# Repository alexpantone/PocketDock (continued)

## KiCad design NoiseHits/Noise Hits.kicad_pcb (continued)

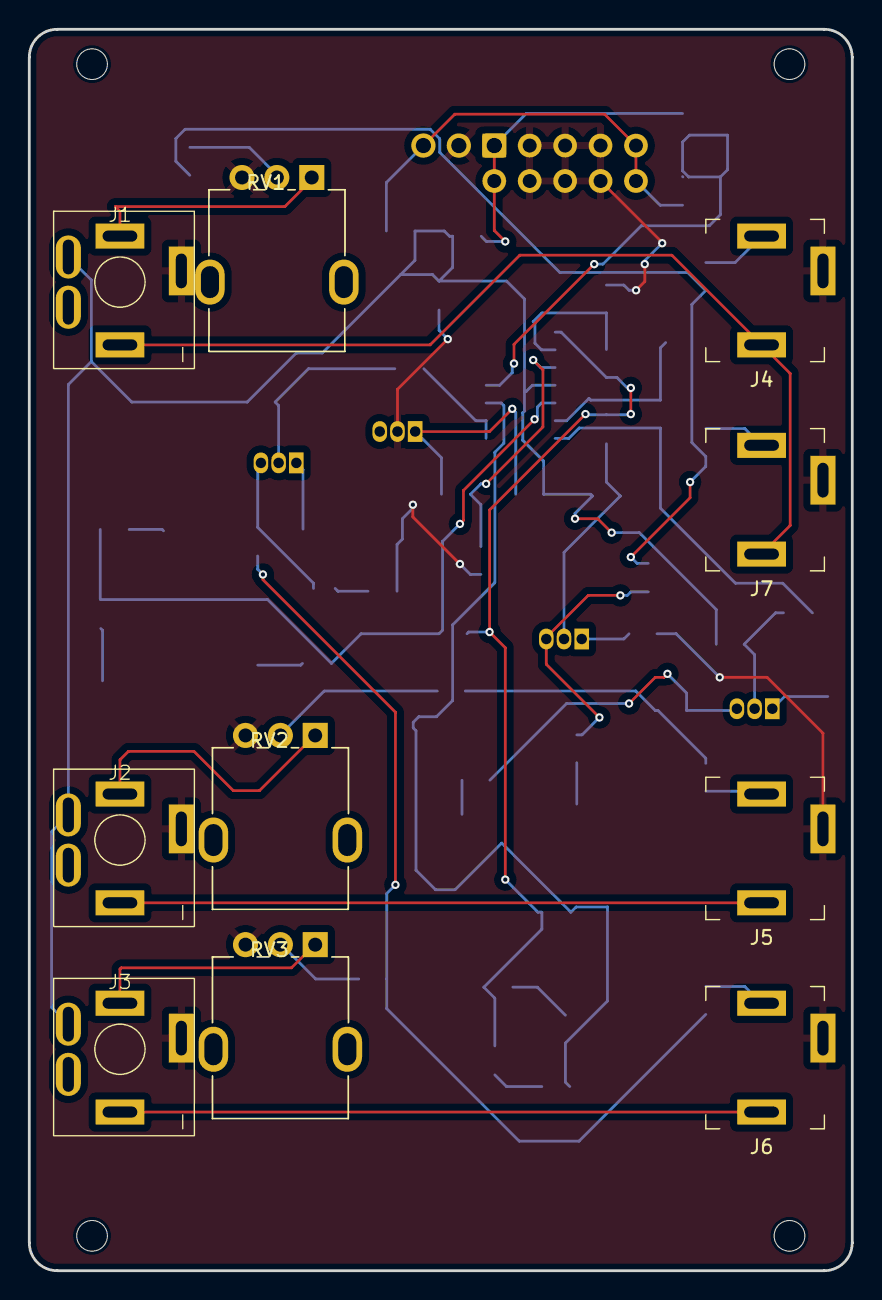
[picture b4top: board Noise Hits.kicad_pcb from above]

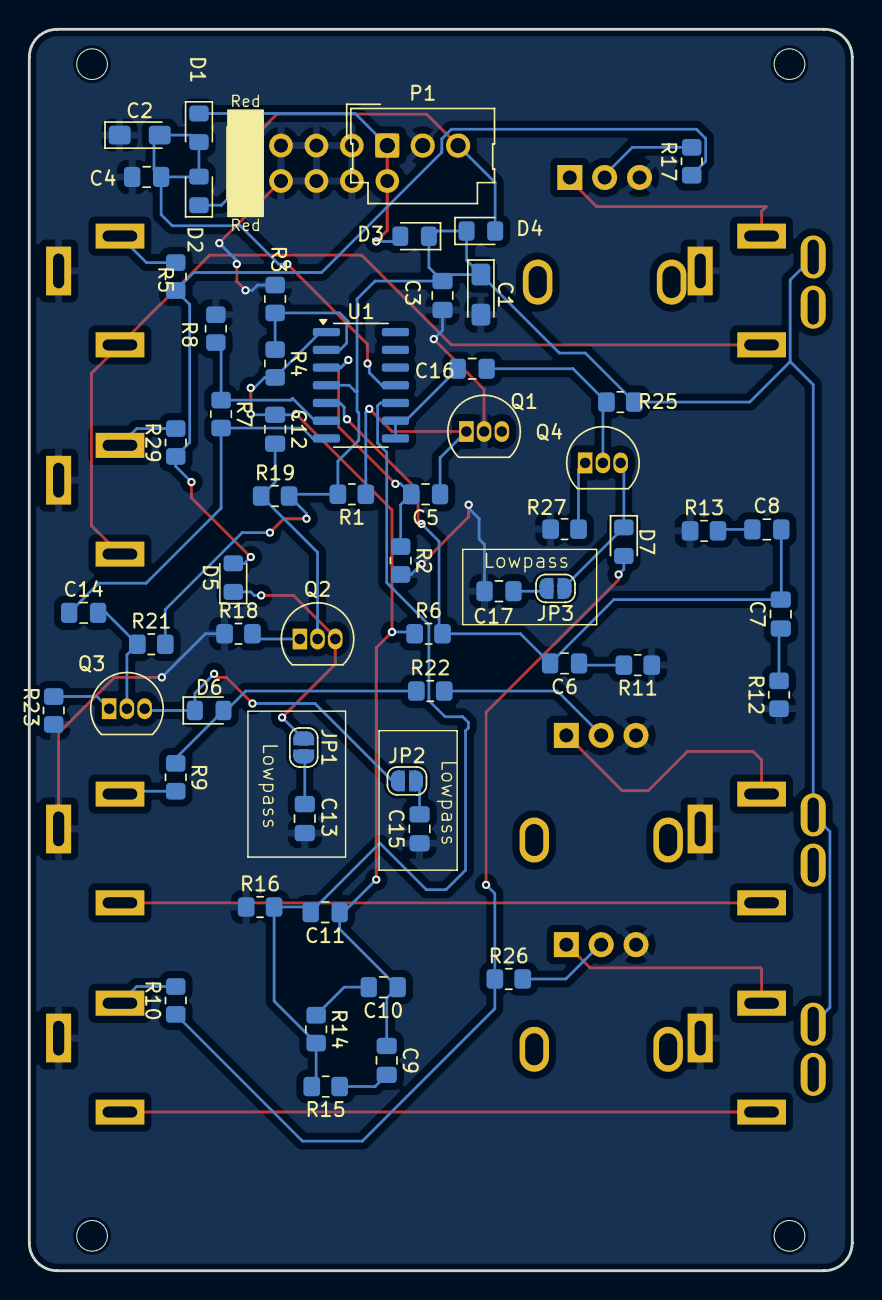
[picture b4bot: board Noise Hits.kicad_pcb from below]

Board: 2 copper layers, 59.0 x 89.0 mm, 74 parts (60 on the bottom side), 47 nets.

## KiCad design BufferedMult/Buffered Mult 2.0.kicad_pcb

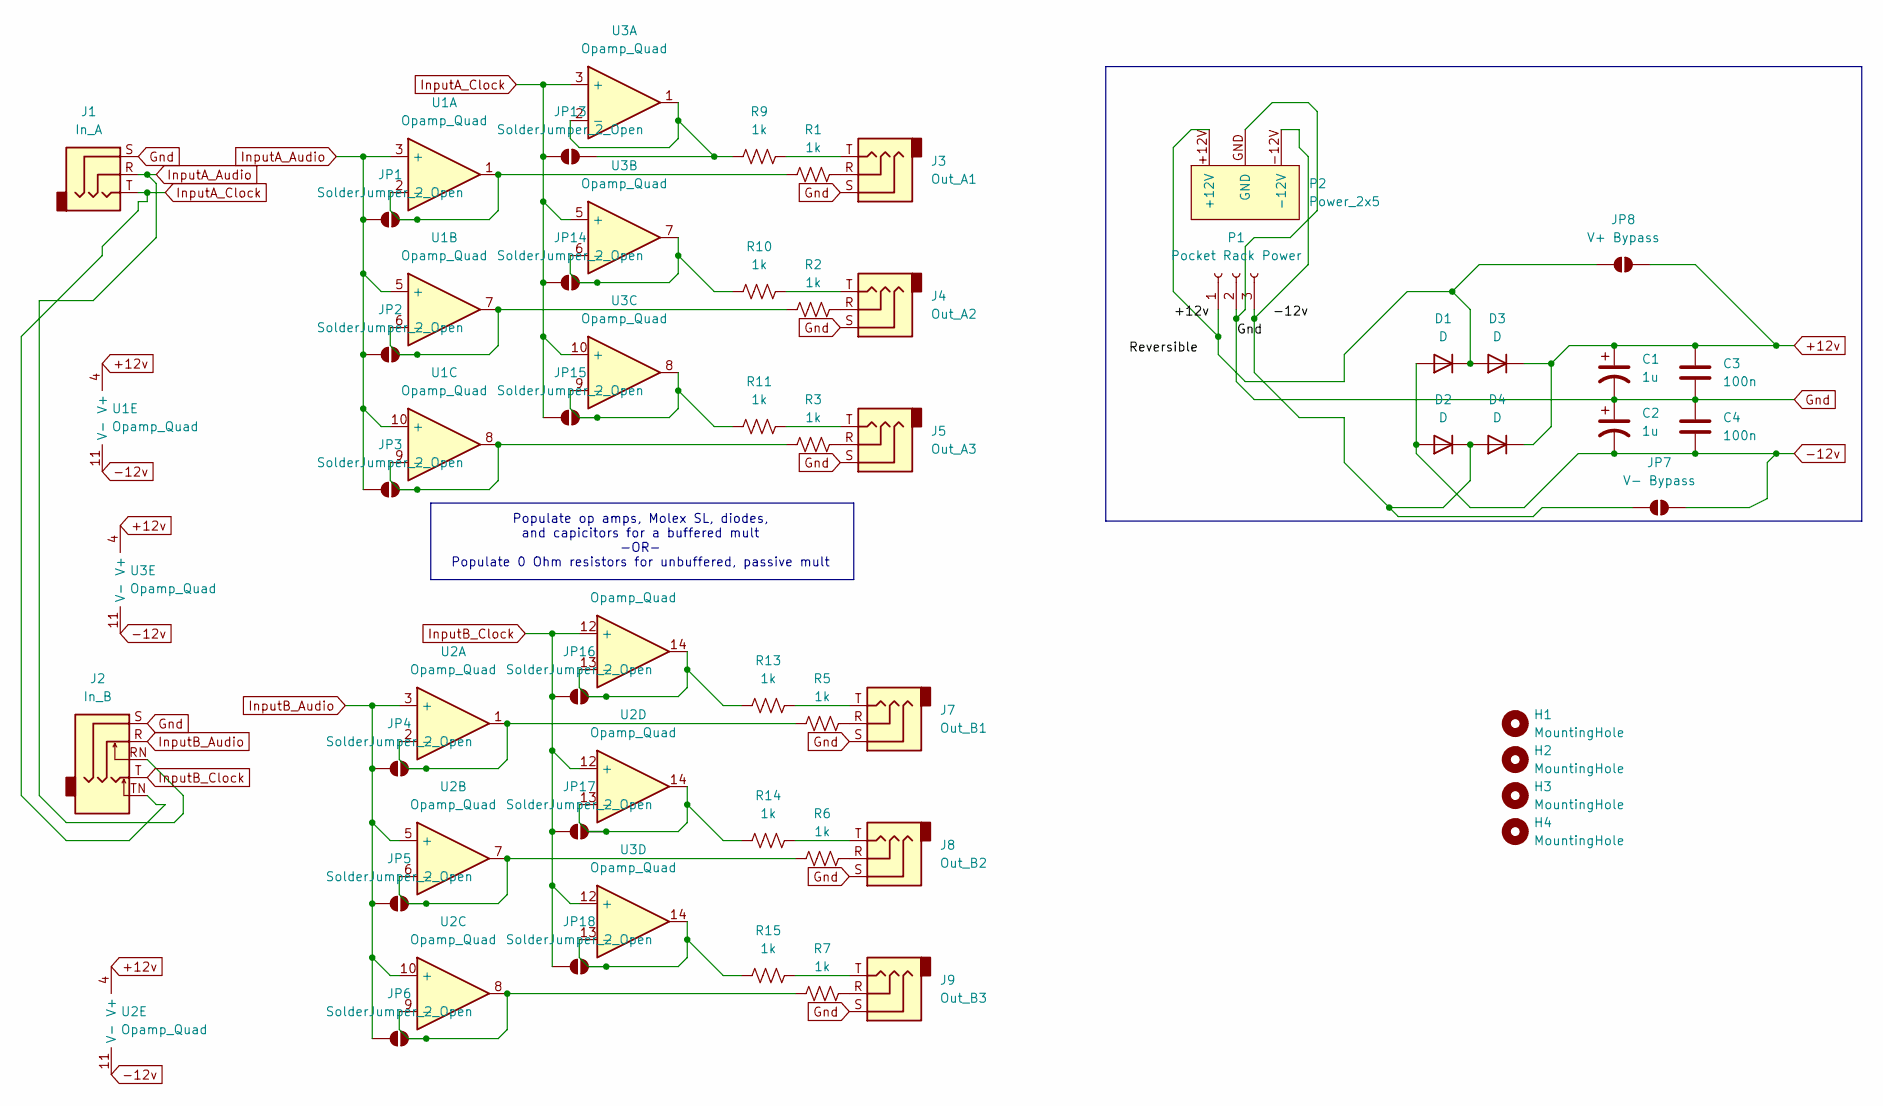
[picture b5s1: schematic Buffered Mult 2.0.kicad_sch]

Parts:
C1, C2: 1u; CP_EIA-3216-10_Kemet-I_Pad1.58x1.35mm_HandSolder
C3, C4: 100n; C_0805_2012Metric_Pad1.18x1.45mm_HandSolder
D1, D2, D3, D4: D; D_0805_2012Metric_Pad1.15x1.40mm_HandSolder
H1, H2, H3, H4: MountingHole; MountingHole_2.2mm_M2
J1: In_A; Jack_3.5mm_QingPu_WQP-PJ301CM
J2: In_B; Jack_3.5mm_QingPu_WQP-PJ358
J3: Out_A1; Jack_3.5mm_QingPu_WQP-PJ301CM
J4: Out_A2; Jack_3.5mm_QingPu_WQP-PJ301CM
J5: Out_A3; Jack_3.5mm_QingPu_WQP-PJ301CM
J7: Out_B1; Jack_3.5mm_QingPu_WQP-PJ301CM
J8: Out_B2; Jack_3.5mm_QingPu_WQP-PJ301CM
J9: Out_B3; Jack_3.5mm_QingPu_WQP-PJ301CM
JP1, JP2, JP3, JP4, JP5, JP6, JP13, JP14, JP15, JP16, JP17, JP18: SolderJumper_2_Open; SolderJumper-2_P1.3mm_Open_Pad1.0x1.5mm
JP7: V- Bypass; SolderJumper-2_P1.3mm_Open_TrianglePad1.0x1.5mm
JP8: V+ Bypass; SolderJumper-2_P1.3mm_Open_TrianglePad1.0x1.5mm
P1: Pocket Rack Power; Molex_SL_171971-0003_1x03_P2.54mm_Vertical
P2: Power_2x5; Power_2x5_Vertical
R1, R2, R3, R5, R6, R7, R9, R10, R11, R13, R14, R15: 1k; R_0805_2012Metric_Pad1.20x1.40mm_HandSolder
U1, U2, U3: Opamp_Quad; SOIC-14_3.9x8.7mm_P1.27mm

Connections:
+12v: C1.1, C3.1, D3.1 (K), D4.1 (K), JP8.2 (B), U1.4 (V+), U2.4 (V+), U3.4 (V+)
-12v: C2.2, C4.2, D1.2 (A), D2.2 (A), JP7.2 (B), U1.11 (V-), U2.11 (V-), U3.11 (V-)
Gnd: C1.2, C2.1, C3.2, C4.1, J1.S, J2.S, J3.S, J4.S, J5.S, J7.S, J8.S, J9.S, P1.2, P2.GND
InputA_Audio: J1.R, J2.RN, JP1.1 (A), JP2.1 (A), JP3.1 (A), U1.3 (+), U1.5 (+), U1.10 (+)
InputA_Clock: J1.T, J2.TN, JP13.1 (A), JP14.1 (A), JP15.1 (A), U3.3 (+), U3.5 (+), U3.10 (+)
InputB_Audio: J2.R, JP4.1 (A), JP5.1 (A), JP6.1 (A), U2.3 (+), U2.5 (+), U2.10 (+)
InputB_Clock: J2.T, JP16.1 (A), JP17.1 (A), JP18.1 (A), U1.12 (+), U2.12 (+), U3.12 (+)
unnamed: D1.1 (K), D3.2 (A), JP8.1 (A), P1.1, P2.+12V
unnamed: D2.1 (K), D4.2 (A), JP7.1 (A), P1.3, P2.-12V
unnamed: J3.R, R1.2
unnamed: J3.T, R9.2
unnamed: J4.R, R2.2
unnamed: J4.T, R10.2
unnamed: J5.R, R3.2
unnamed: J5.T, R11.2
unnamed: J7.R, R5.2
unnamed: J7.T, R13.2
unnamed: J8.R, R6.2
unnamed: J8.T, R14.2
unnamed: J9.R, R7.2
unnamed: J9.T, R15.2
unnamed: JP1.2 (B), R1.1, U1.1, U1.2 (-)
unnamed: JP2.2 (B), R2.1, U1.6 (-), U1.7
unnamed: JP3.2 (B), R3.1, U1.8, U1.9 (-)
unnamed: JP4.2 (B), R5.1, U2.1, U2.2 (-)
unnamed: JP5.2 (B), R6.1, U2.6 (-), U2.7
unnamed: JP6.2 (B), R7.1, U2.8, U2.9 (-)
unnamed: JP13.2 (B), R9.1, U3.1, U3.2 (-)
unnamed: JP14.2 (B), R10.1, U3.6 (-), U3.7
unnamed: JP15.2 (B), R11.1, U3.8, U3.9 (-)
unnamed: JP16.2 (B), R13.1, U1.13 (-), U1.14
unnamed: JP17.2 (B), R14.1, U2.13 (-), U2.14
unnamed: JP18.2 (B), R15.1, U3.13 (-), U3.14

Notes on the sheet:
Populate op amps, Molex SL, diodes, and capicitors for a buffered mult -OR- Populate 0 Ohm resistors for unbuffered, passive mult

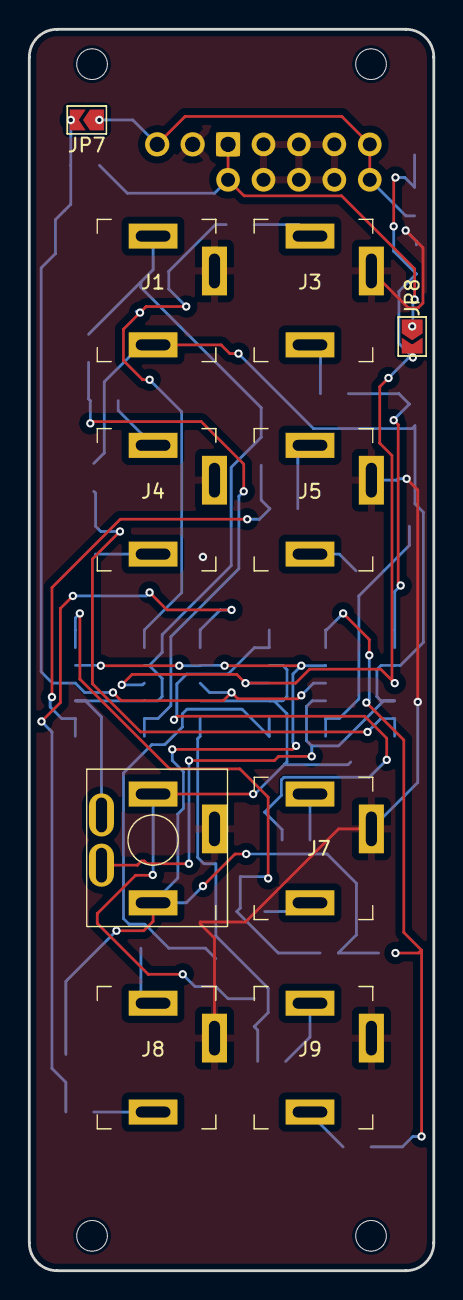
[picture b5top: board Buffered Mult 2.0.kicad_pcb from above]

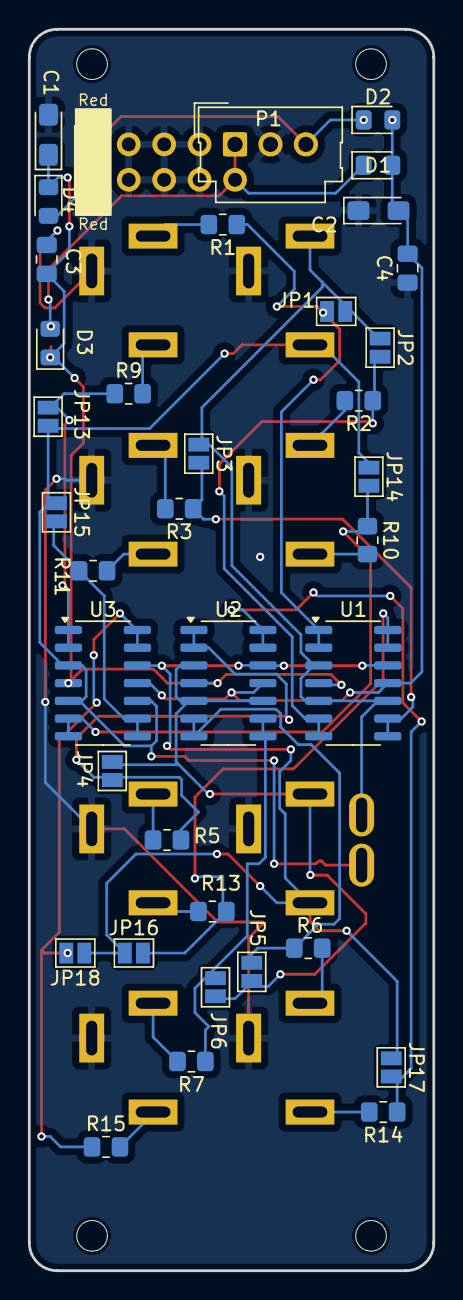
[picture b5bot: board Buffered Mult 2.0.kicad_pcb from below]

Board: 2 copper layers, 29.0 x 89.0 mm, 51 parts (37 on the bottom side), 33 nets.

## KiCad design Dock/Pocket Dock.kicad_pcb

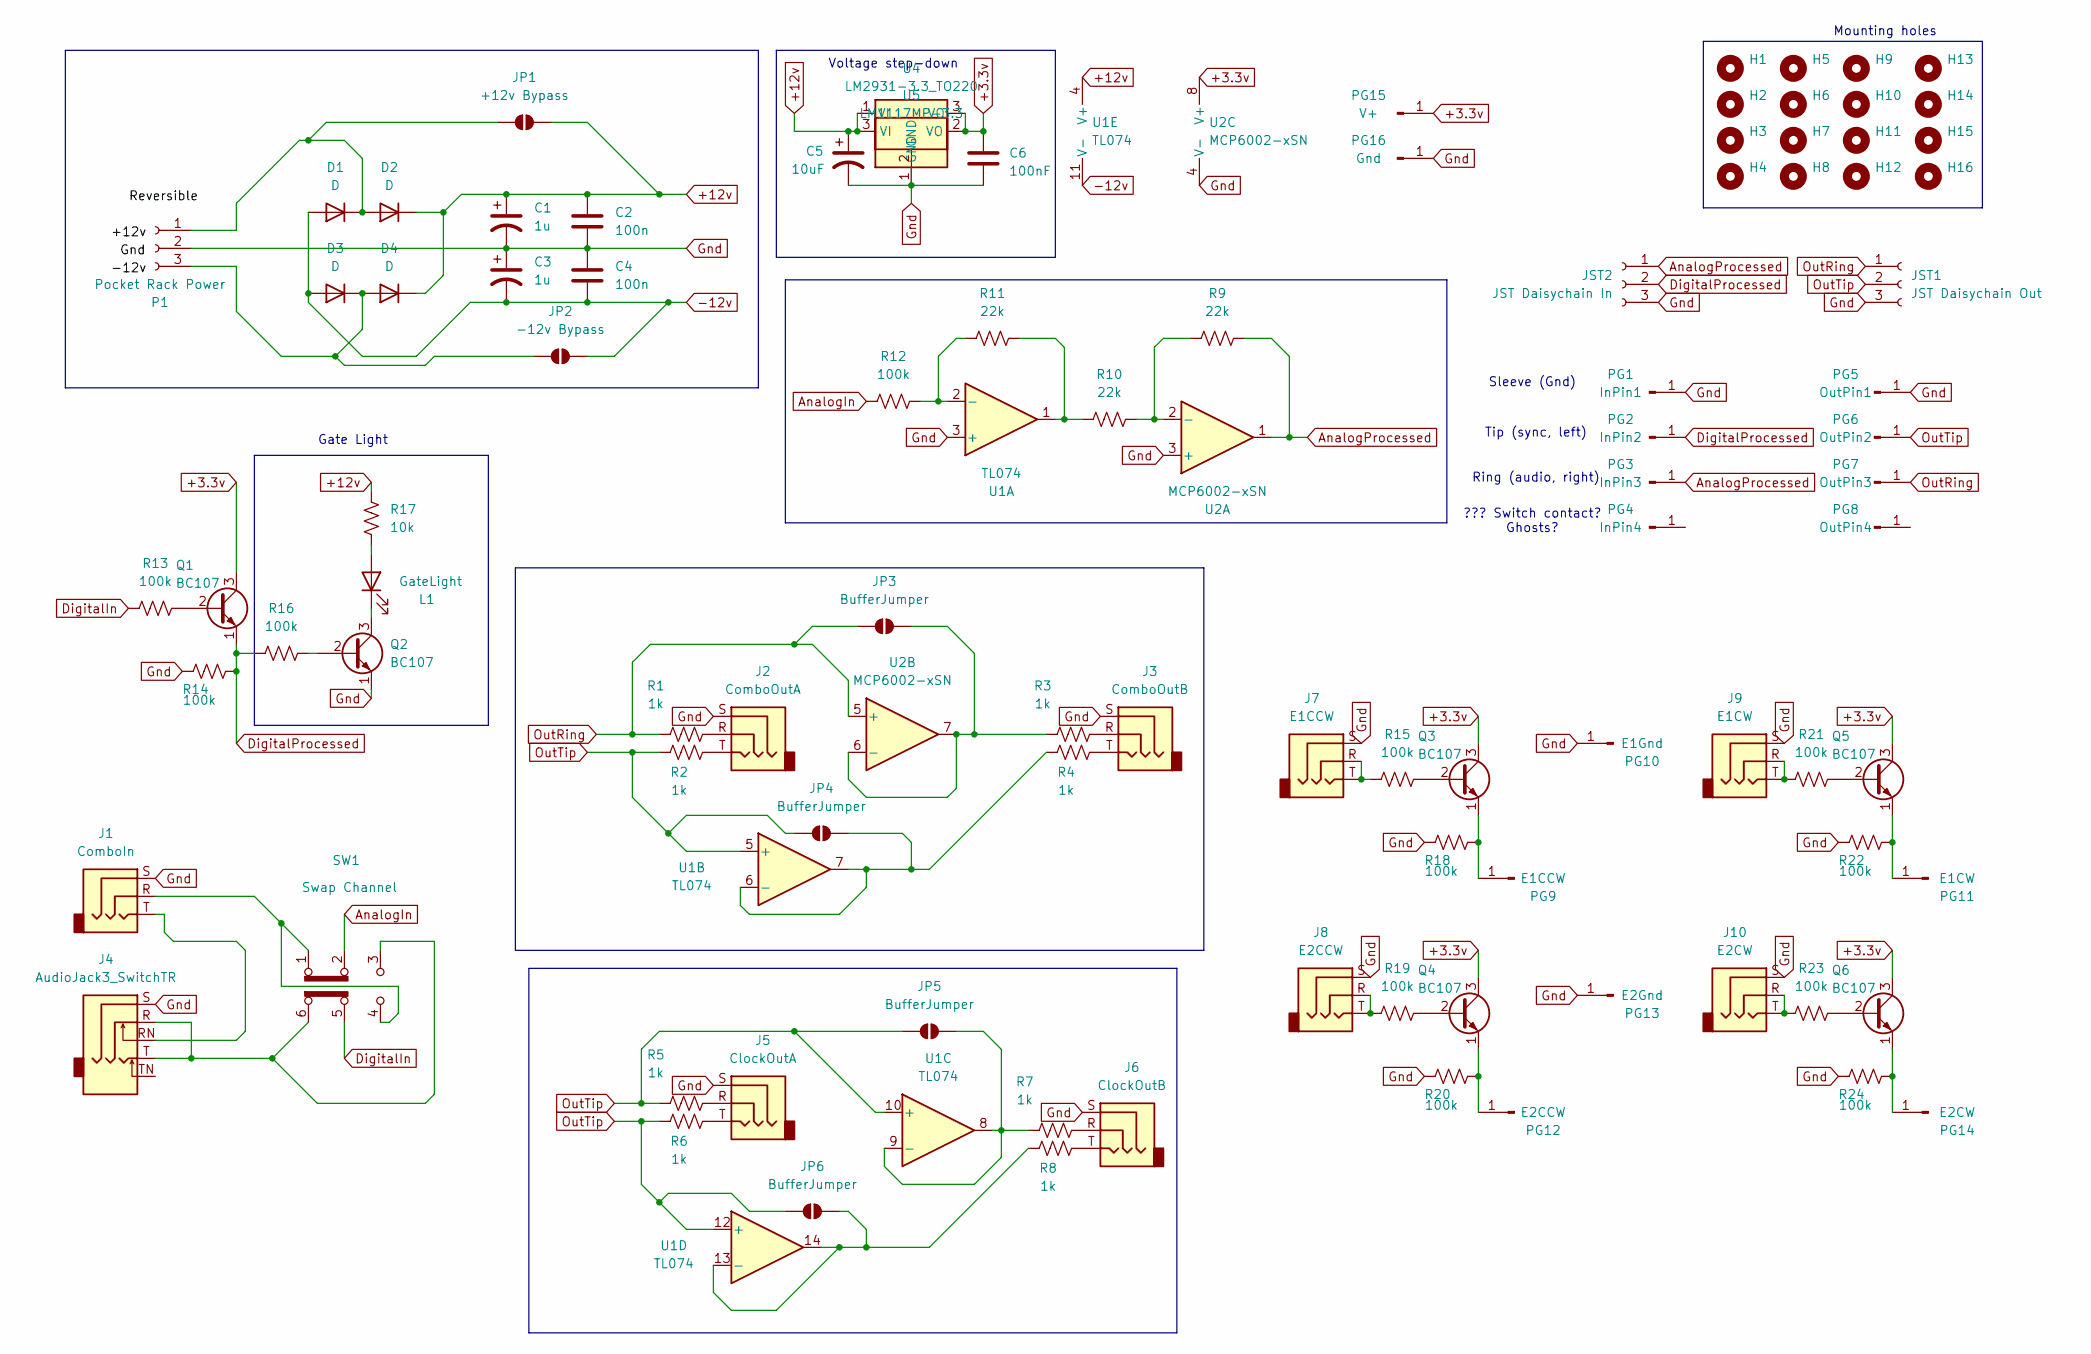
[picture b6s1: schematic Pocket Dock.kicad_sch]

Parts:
C1, C3: 1u; CP_EIA-3216-10_Kemet-I_Pad1.58x1.35mm_HandSolder
C2, C4: 100n; C_0805_2012Metric_Pad1.18x1.45mm_HandSolder
C5: 10uF; C_0805_2012Metric_Pad1.18x1.45mm_HandSolder
C6: 100nF; C_0805_2012Metric_Pad1.18x1.45mm_HandSolder
D1, D2, D3, D4: D; D_0805_2012Metric_Pad1.15x1.40mm_HandSolder
H1, H2, H3, H4, H5, H6, H7, H8, H9, H10, H11, H12, H13, H14, H15, H16: MountingHole; MountingHole_2.2mm_M2
J1: ComboIn; Jack_3.5mm_QingPu_WQP-PJ301CM
J2: ComboOutA; Jack_3.5mm_QingPu_WQP-PJ301CM
J3: ComboOutB; Jack_3.5mm_QingPu_WQP-PJ301CM
J4: AudioJack3_SwitchTR; Jack_3.5mm_QingPu_WQP-PJ358
J5: ClockOutA; Jack_3.5mm_QingPu_WQP-PJ301CM
J6: ClockOutB; Jack_3.5mm_QingPu_WQP-PJ301CM
J7: E1CCW; Jack_3.5mm_QingPu_WQP-PJ301CM
J8: E2CCW; Jack_3.5mm_QingPu_WQP-PJ301CM
J9: E1CW; Jack_3.5mm_QingPu_WQP-PJ301CM
J10: E2CW; Jack_3.5mm_QingPu_WQP-PJ301CM
JP1: +12v Bypass; SolderJumper-2_P1.3mm_Open_TrianglePad1.0x1.5mm
JP2: -12v Bypass; SolderJumper-2_P1.3mm_Open_TrianglePad1.0x1.5mm
JP3, JP4, JP5, JP6: BufferJumper; SolderJumper-2_P1.3mm_Open_RoundedPad1.0x1.5mm
JST1: JST Daisychain Out; JST_XH_B3B-XH-A_1x03_P2.50mm_Vertical
JST2: JST Daisychain In; JST_XH_B3B-XH-A_1x03_P2.50mm_Vertical
L1: GateLight; LED_D3.0mm
P1: Pocket Rack Power; Molex_SL_171971-0003_1x03_P2.54mm_Vertical
PG1: InPin1; PinHeader_1x01_P2.00mm_Vertical
PG2: InPin2; PinHeader_1x01_P2.00mm_Vertical
PG3: InPin3; PinHeader_1x01_P2.00mm_Vertical
PG4: InPin4; PinHeader_1x01_P2.00mm_Vertical
PG5: OutPin1; PinHeader_1x01_P2.00mm_Vertical
PG6: OutPin2; PinHeader_1x01_P2.00mm_Vertical
PG7: OutPin3; PinHeader_1x01_P2.00mm_Vertical
PG8: OutPin4; PinHeader_1x01_P2.00mm_Vertical
PG9: E1CCW; PinHeader_1x01_P2.00mm_Vertical
PG10: E1Gnd; PinHeader_1x01_P2.00mm_Vertical
PG11: E1CW; PinHeader_1x01_P2.00mm_Vertical
PG12: E2CCW; PinHeader_1x01_P2.00mm_Vertical
PG13: E2Gnd; PinHeader_1x01_P2.00mm_Vertical
PG14: E2CW; PinHeader_1x01_P2.00mm_Vertical
PG15: V+; PinHeader_1x01_P2.00mm_Vertical
PG16: Gnd; PinHeader_1x01_P2.00mm_Vertical
Q1, Q2, Q3, Q4, Q5, Q6: BC107; SC-59_Handsoldering
R1, R2, R3, R4, R5, R6, R7, R8: 1k; R_0805_2012Metric_Pad1.20x1.40mm_HandSolder
R9, R10, R11: 22k; R_0805_2012Metric_Pad1.20x1.40mm_HandSolder
R12, R13, R14, R15, R16, R18, R19, R20, R21, R22, R23, R24: 100k; R_0805_2012Metric_Pad1.20x1.40mm_HandSolder
R17: 10k; R_0805_2012Metric_Pad1.20x1.40mm_HandSolder
SW1: Swap Channel; SW_E-Switch_EG1271_SPDT
U1: TL074; SOIC-14_3.9x8.7mm_P1.27mm
U2: MCP6002-xSN; SOIC-8_3.9x4.9mm_P1.27mm
U4: LM2931-3.3_TO220; TO-220-3_Vertical
U5: LM1117MP-3.3; SOT-223-3_TabPin2

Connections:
+3.3v: C6.1, PG15.1, Q1.3 (C), Q3.3 (C), Q4.3 (C), Q5.3 (C), Q6.3 (C), U2.8 (V+), U4.3 (VO), U5.2 (VO)
+12v: C1.1, C2.1, C5.1, D2.1 (K), D4.1 (K), JP1.2 (B), R17.1, U1.4 (V+), U4.1 (VI), U5.3 (VI)
-12v: C3.2, C4.2, D1.2 (A), D3.2 (A), JP2.2 (B), U1.11 (V-)
AnalogIn: R12.1, SW1.2 (B)
AnalogProcessed: JST2.1, PG3.1, R9.2, U2.1
DigitalIn: R13.2, SW1.5 (B)
DigitalProcessed: JST2.2, PG2.1, Q1.1 (E), R14.2, R16.1
Gnd: C1.2, C2.2, C3.1, C4.1, C5.2, C6.2, J1.S, J2.S, J3.S, J4.S, J5.S, J6.S, J7.S, J8.S, J9.S, J10.S, JST1.3, JST2.3, P1.2, PG1.1, PG5.1, PG10.1, PG13.1, PG16.1, Q2.1 (E), R14.1, R18.1, R20.1, R22.1, R24.1, U1.3 (+), U2.3 (+), U2.4 (V-), U4.2 (GND), U5.1 (GND)
unnamed: D1.1 (K), D2.2 (A), JP1.1 (A), P1.1
unnamed: D3.1 (K), D4.2 (A), JP2.1 (A), P1.3
unnamed: J1.R, SW1.1 (A), SW1.4 (A)
unnamed: J1.T, J4.RN
unnamed: J2.R, R1.2
unnamed: J2.T, R2.2
unnamed: J3.R, R3.2
unnamed: J3.T, R4.2
unnamed: J4.R, J4.T, SW1.3 (C), SW1.6 (C)
unnamed: J5.R, R5.2
unnamed: J5.T, R6.2
unnamed: J6.R, R7.2
unnamed: J6.T, R8.2
unnamed: J7.R, J7.T, R15.2
unnamed: J8.R, J8.T, R19.2
unnamed: J9.R, J9.T, R21.2
unnamed: J10.R, J10.T, R23.2
unnamed: JP3.2 (B), R3.1, U2.6 (-), U2.7
unnamed: JP4.2 (B), R4.1, U1.6 (-), U1.7
unnamed: JP5.2 (B), R7.1, U1.8, U1.9 (-)
unnamed: JP6.2 (B), R8.1, U1.13 (-), U1.14
unnamed: L1.2 (A), R17.2
unnamed: L1.1 (K), Q2.3 (C)
unnamed: PG9.1, Q3.1 (E), R18.2
unnamed: PG11.1, Q5.1 (E), R22.2
unnamed: PG12.1, Q4.1 (E), R20.2
unnamed: PG14.1, Q6.1 (E), R24.2
unnamed: Q1.2 (B), R13.1
unnamed: Q2.2 (B), R16.2
unnamed: Q3.2 (B), R15.1
unnamed: Q4.2 (B), R19.1
unnamed: Q5.2 (B), R21.1
unnamed: Q6.2 (B), R23.1
unnamed: R10.1, R11.2, U1.1
unnamed: R11.1, R12.2, U1.2 (-)
unnamed: R9.1, R10.2, U2.2 (-)
OutRing: JP3.1 (A), JST1.1, PG7.1, R1.1, U2.5 (+)
OutTip: JP4.1 (A), JP5.1 (A), JP6.1 (A), JST1.2, PG6.1, R2.1, R5.1, R6.1, U1.5 (+), U1.10 (+), U1.12 (+)

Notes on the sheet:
Mounting holes
??? Switch contact? Ghosts?
Ring (audio, right)
Gate Light
Voltage step-down
Sleeve (Gnd)
Tip (sync, left)

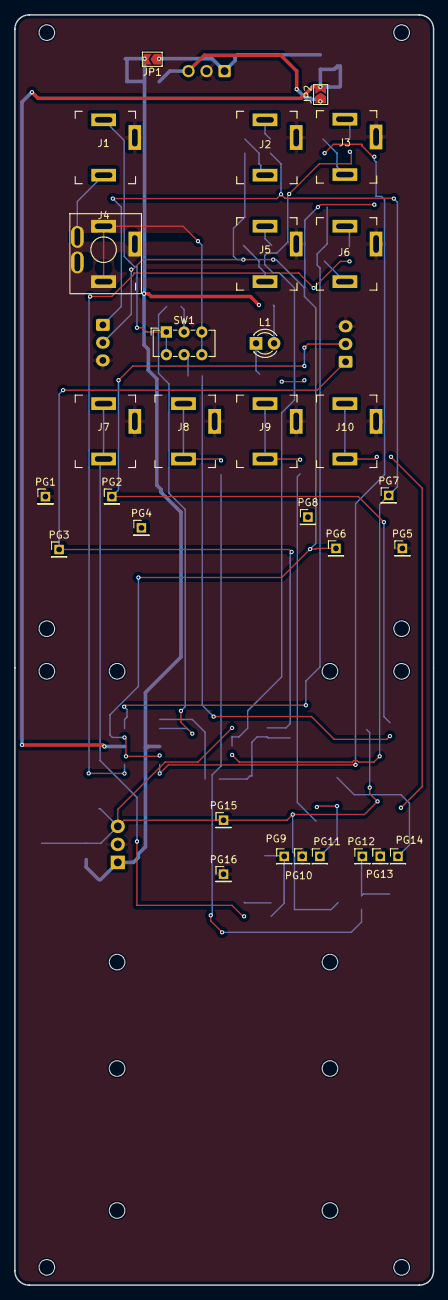
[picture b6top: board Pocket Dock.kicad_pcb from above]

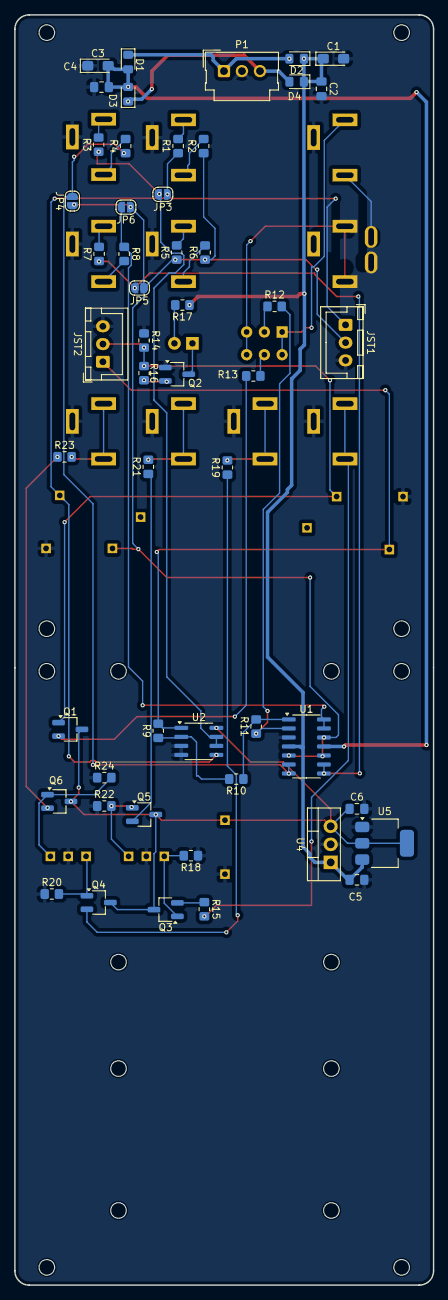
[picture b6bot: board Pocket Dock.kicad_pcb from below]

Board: 2 copper layers, 59.0 x 179.0 mm, 97 parts (51 on the bottom side), 46 nets.

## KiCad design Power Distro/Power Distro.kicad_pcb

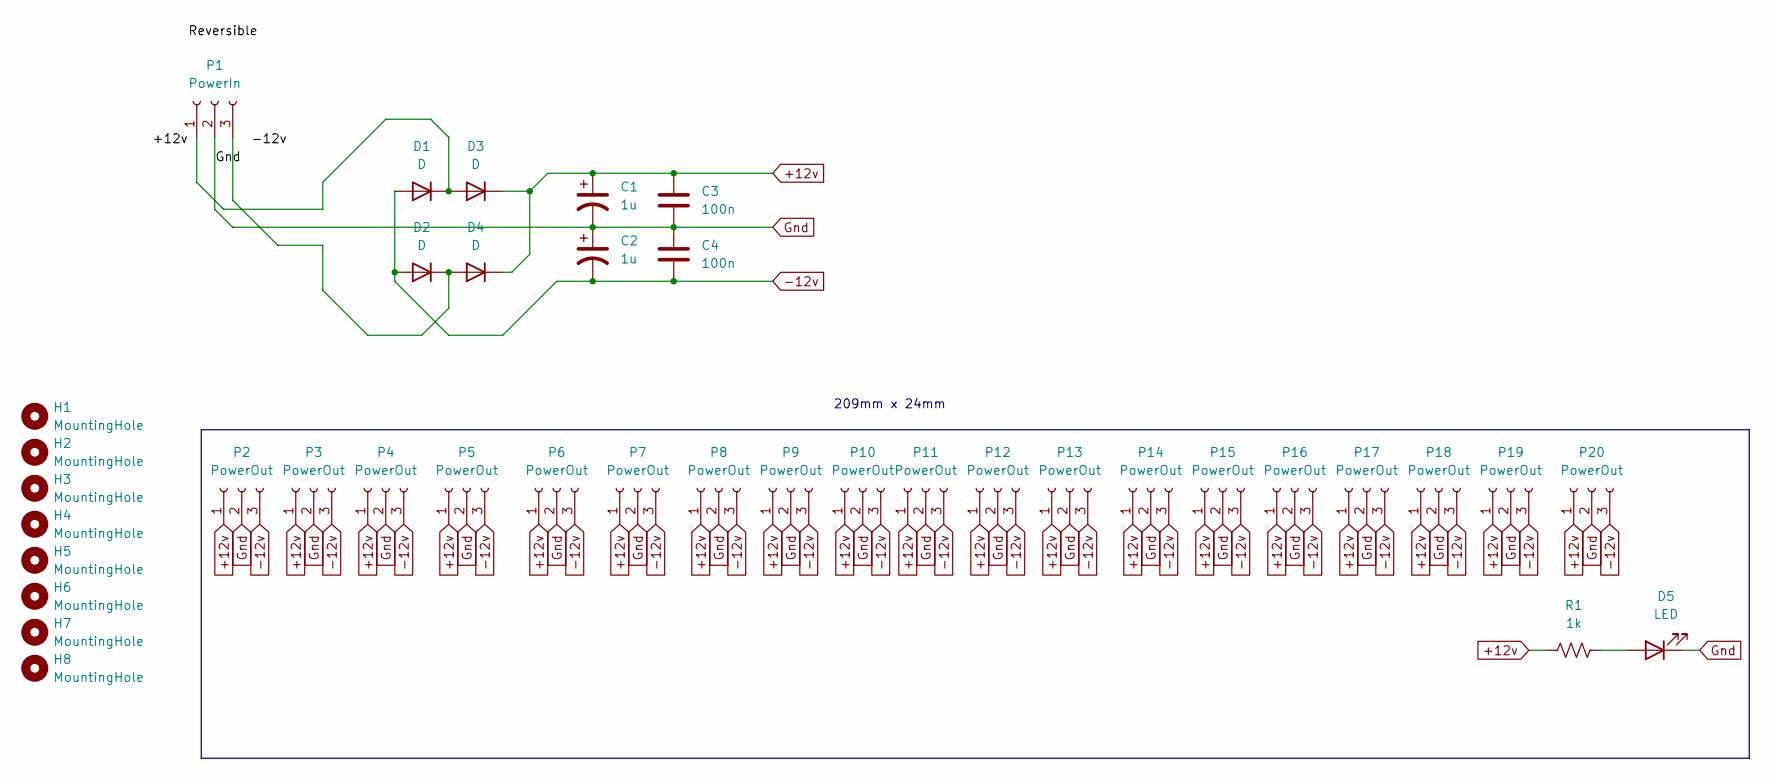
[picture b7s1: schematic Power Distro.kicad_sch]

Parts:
C1, C2: 1u; CP_EIA-3216-10_Kemet-I_Pad1.58x1.35mm_HandSolder
C3, C4: 100n; C_0805_2012Metric_Pad1.18x1.45mm_HandSolder
D1, D2, D3, D4: D; D_0805_2012Metric_Pad1.15x1.40mm_HandSolder
D5: LED; LED_D1.8mm_W3.3mm_H2.4mm
H1, H2, H3, H4, H5, H6, H7, H8: MountingHole; MountingHole_2.2mm_M2
P1: PowerIn; Molex_SL Pocket Rack_1x03_P2.54mm_Vertical
P2, P3, P4, P5, P6, P7, P8, P9, P10, P11, P12, P13, P14, P15, P16, P17, P18, P19, P20: PowerOut; Molex_SL Pocket Rack_1x03_P2.54mm_Vertical
R1: 1k; R_0805_2012Metric_Pad1.20x1.40mm_HandSolder

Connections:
+12v: C1.1, C3.1, D3.1 (K), D4.1 (K), P2.1, P3.1, P4.1, P5.1, P6.1, P7.1, P8.1, P9.1, P10.1, P11.1, P12.1, P13.1, P14.1, P15.1, P16.1, P17.1, P18.1, P19.1, P20.1, R1.1
-12v: C2.2, C4.2, D1.2 (A), D2.2 (A), P2.3, P3.3, P4.3, P5.3, P6.3, P7.3, P8.3, P9.3, P10.3, P11.3, P12.3, P13.3, P14.3, P15.3, P16.3, P17.3, P18.3, P19.3, P20.3
Gnd: C1.2, C2.1, C3.2, C4.1, D5.1 (K), P1.2, P2.2, P3.2, P4.2, P5.2, P6.2, P7.2, P8.2, P9.2, P10.2, P11.2, P12.2, P13.2, P14.2, P15.2, P16.2, P17.2, P18.2, P19.2, P20.2
unnamed: D1.1 (K), D3.2 (A), P1.1
unnamed: D2.1 (K), D4.2 (A), P1.3
unnamed: D5.2 (A), R1.2

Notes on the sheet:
209mm x 24mm

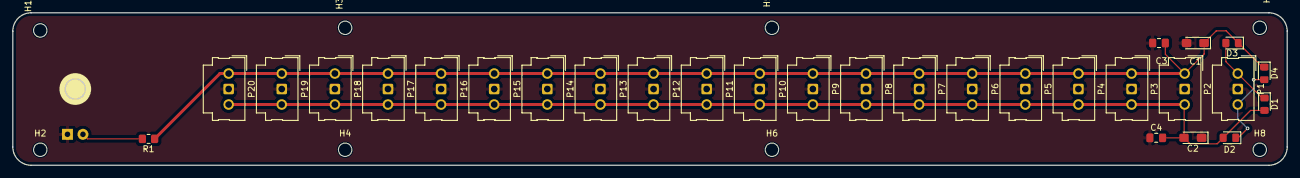
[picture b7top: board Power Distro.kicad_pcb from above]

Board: 2 copper layers, 209.0 x 25.0 mm, 38 parts (1 on the bottom side), 6 nets.
